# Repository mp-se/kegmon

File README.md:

# KegMon - Monitoring the volume in your kegs

This is a project that I have done for my own Keezer, if you like it please feel free to suggest improvements. 

For docs see: https://mp-se.github.io/kegmon/index.html

# Hardware

* Supports ESP8266 D1 mini, ESP32s2 mini or ESP32s3 mini
* Loadcells and HX711/NAU7802 ADC converters
* DS18B20, DHT22, BME280 or BrewPI(IP) temperature sensors
* OLED 0.96" or LCD 20x4/20x2 displays

# Features

* Can measure weight from 1 or 2 scales
* Stable scale presentation (data is filtered and processed)
* Support temperature/humidity sensor in one scale base
* Integration with Brewfather to retrive data on brew
* Integration with Brewspy to retrive data on brew and also update the remaning volume and pours
* Integration with Home Assistant
* Weights and Volumes in Metric, Imperial (both US and UK)
* Pour detection for pours over 100 ml
* Estimation on how many glasses remain in the kegs
* Firmware update via UI
* One build for all hardware options
* Modern HTML5 UI
* Easy scale calibration
* 3D models and PCB

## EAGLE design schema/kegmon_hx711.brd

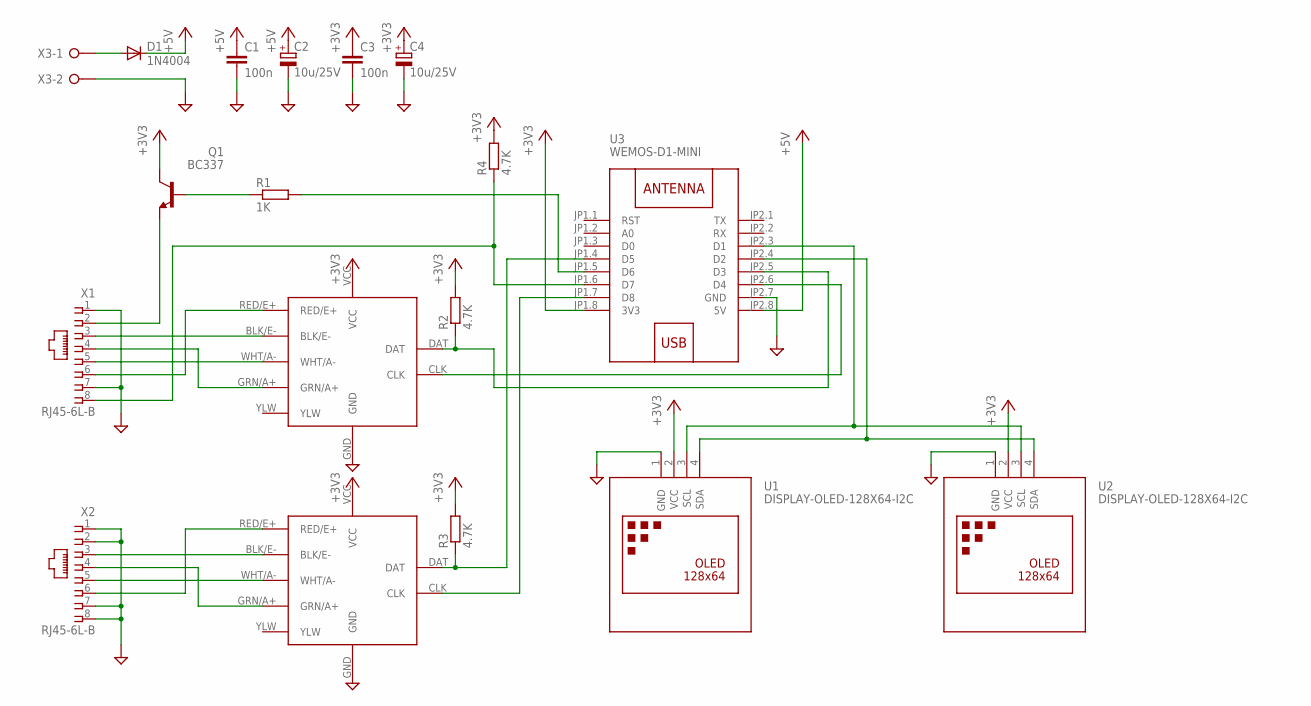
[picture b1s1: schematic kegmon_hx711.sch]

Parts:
C1, C3: 100n; C050-025X075
C2, C4: 10u/25V; E2,5-5
D1: 1N4004; DO41-10
IC1, IC2: SPARKFUN-HX711
Q1: BC337; TO92
R1: 1K; 0207/10
R2, R3, R4: 4.7K; 0207/10
U1, U2: DISPLAY-OLED-128X64-I2C; DISPLAY-OLED-128X64-I2C-NOHOLES
U3: WEMOS-D1-MINI
X1, X2: RJ45-6L-B; RJ45-NO-SHIELD
X3: W237-02P; W237-132

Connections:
+3V3: C3.1, C4.+, IC1.VCC, IC2.VCC, Q1.3 (C), R2.2, R3.2, R4.2, U1.2 (VCC), U2.2 (VCC), U3.JP1.8 (3V3)
+5V: C1.1, C2.+, D1.C, U3.JP2.8 (5V)
GND: C1.2, C2.-, C3.2, C4.-, IC1.GND, IC2.GND, U1.1 (GND), U2.1 (GND), U3.JP2.7 (GND), X1.1, X1.7, X2.1, X2.2, X2.7, X2.8, X3.2
unnamed: Q1.2 (B), R1.1
unnamed: U1.3 (SCL), U2.3 (SCL), U3.JP2.3 (D1)
unnamed: D1.A, X3.1
unnamed: IC1.RED/E+, X1.6
unnamed: IC1.BLK/E-, X1.3
unnamed: R4.1, U3.JP1.6 (D7), X1.8
unnamed: IC1.WHT/A-, X1.5
unnamed: IC1.GRN/A+, X1.4
unnamed: IC2.BLK/E-, X2.3
unnamed: IC2.RED/E+, X2.6
unnamed: IC2.GRN/A+, X2.4
unnamed: IC2.WHT/A-, X2.5
unnamed: IC1.DAT, R2.1, U3.JP2.5 (D3)
unnamed: IC1.CLK, U3.JP2.6 (D4)
unnamed: IC2.DAT, R3.1, U3.JP1.4 (D5)
unnamed: IC2.CLK, U3.JP1.7 (D8)
unnamed: U1.4 (SDA), U2.4 (SDA), U3.JP2.4 (D2)
unnamed: Q1.1 (E), X1.2
unnamed: R1.2, U3.JP1.5 (D6)

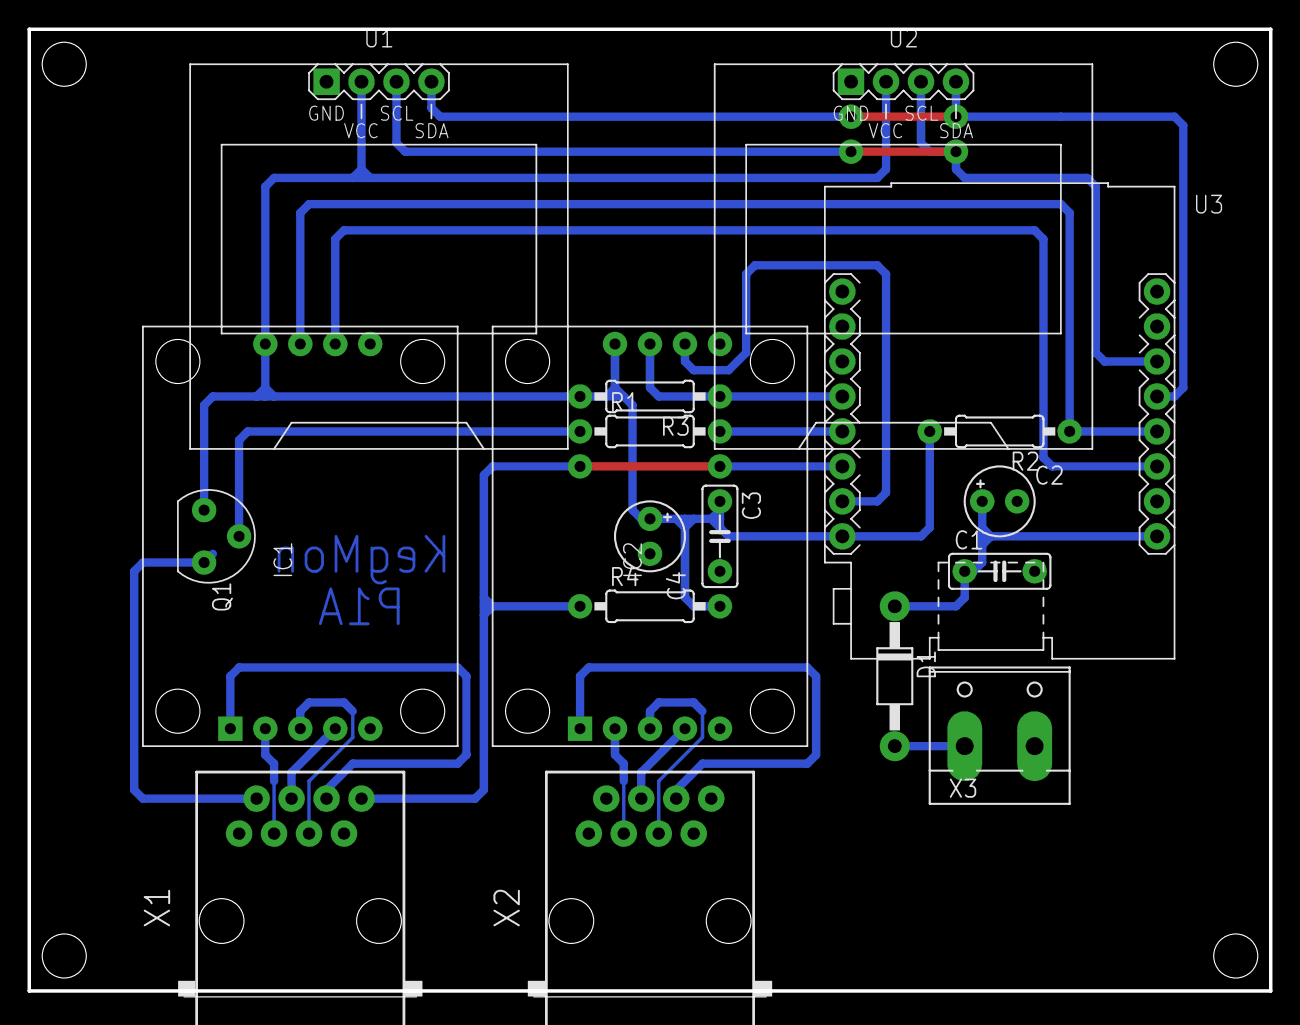
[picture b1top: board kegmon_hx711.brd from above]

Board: 2 copper layers, 90.2 x 69.8 mm, 18 parts (0 on the bottom side), 22 nets.

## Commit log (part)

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2023-03-16 GitHub Action Build
2023-03-16 Increase json buffer size
2023-03-16 Lint fixes
2023-03-16 Update documentation
2023-03-18 Added link to alternative scale base.
2023-03-19 Updated hardware docs
2023-03-20 Removed humidity when ds18b20 is used
2023-03-20 HW doc update
2023-03-20 Updated platformio
2023-03-20 Update doc date
2023-04-11 Adding hardware testing target
2023-04-11 Adding option to bypass scale validations
2023-04-11 Precommit fixes
2023-04-11 Added mobile dashboard
2023-04-11 Added schema and pcb for HX711
2023-04-11 Updated release notes for 0.6
2023-04-11 Updated project config
2023-04-24 Added dashboard, pcb and case
2023-04-27 Updated docs for release
2023-05-04 Added progress bar on dashboard
2023-05-05 Added driver for LCD 20x4
2023-05-05 Added new display option
2023-05-06 Added layout for single display + lcd build
2023-05-06 Fix precommit
2023-05-08 Merged into one build
2023-05-08 0.7b2
2023-05-08 Remove lcb bins
2023-05-10 Updated layout
2023-05-20 Doc updates for LCB
2023-05-20 Refactored display layout into own class
2023-05-20 Adjusted formatting for lcd
2023-05-21 Updated docs with respect to LCD
2023-05-31 Adding cors header to responses
2023-05-31 Adjusted to new display setup
2023-05-31 Update release notes
2023-05-31 Fixed version number for docs
2023-06-10 Remove duplicated define WS_SEND
2023-06-10 Update arduino versions
2023-06-10 Adding log outputs to level change
2023-06-12 Adding reset reason to s2 + fix bug in influx push
2023-06-12 Fix month+1 in loglevels
2023-06-12 Correct use of espserial wss init
2023-06-12 Adjusted hass device registration
2023-06-13 Update arduino version
2023-06-14 Dont send temp to hass if no sensor is attached
2023-06-19 Added core dump option and startup logging
2023-06-19 Skip level logging if values are zero
2023-06-19 Fix include naming
2023-06-19 Added partition file with coredump partition
2023-06-19 Updated build dependecies
2023-07-30 move code around and split sensors
2023-08-03 Added raw weight on hardware stats
2023-08-03 Updated display layout
2023-08-03 Updated build no
2023-08-03 Updated release notes
2023-08-03 Formatting changes
2023-08-04 Update esp fwk
2023-08-05 use unique_ptr and add logs
2023-08-05 check sensor more often
2023-08-05 replace floats
2023-08-05 Updated dependecies
2023-08-07 Fix include error from PR
2023-08-07 Adjused code to work with esp32
2023-08-08 Updated dependecies and cleanup code
2023-08-09 add code
2023-08-09 add docs
2023-08-16 setup on secondery address too
2023-08-16 remove binary changes
2023-08-18 undo reset changes
2023-08-18 fix formating
2023-08-28 Change default temp sensor
2023-08-28 Update docs
2023-08-28 Update dependecies
2023-08-28 Added bme280 support
2023-08-28 Fix bug in level.cpp
2023-08-28 Updated test payload
2023-08-28 Run precommit
2023-08-28 Updated docs
2023-08-30 Adding option to change pins
2023-08-30 Pins are disabled by default
2023-08-30 precommit
2023-08-31 Adding tooltops
2023-08-31 Fixed build for esp32s2
2023-08-31 Fixed reset logic for temp sensors
2023-08-31 bump version
2023-09-02 Fix config url
2023-09-03 Adding support for wokwi
2023-09-03 Upd esp32 deps
2023-09-03 precommit updates
2023-09-04 Update images for docs
2023-09-04 Bump to beta1
2023-09-06 Update for wokwi debug
2023-09-07 Adding development page to docs
2023-09-08 Update gh
2023-09-08 Update gh action
2023-09-10 Added simple dependemcy checker for libraries
2023-09-10 Update gha for build
2023-09-10 Updated dependency checker
2023-09-12 Update dependency script
2023-09-12 Updated dependencies
2023-09-12 Adding env file for act gh runner
2023-09-13 Fixed error message
2023-09-13 Update version + fix json issues + upd gha
2023-10-04 Using pre-built partition as fs for wokwi
2023-10-04 Bump to release
2023-10-04 Adding condition
2023-10-04 Upd doc ver
2023-10-05 Revert arduino version to 5.4
2023-10-12 Fix issue with dht22 sensor not being detected as missing
2023-10-13 Fix memory leak
2023-10-13 Formatting fix
2023-10-21 Adding brewpi as temp sensor
2023-11-08 Removed dashboard
2023-12-18 Added support for s3 board
2023-12-18 Fix precommit errors
2024-01-26 Add s3 to build
2024-01-27 Fix spelling
2024-01-28 Update (c)
2024-07-14 Remove old UI files
2024-07-14 Update brewspy
2024-07-14 Change config to adapat to new tag format
2024-07-14 Updated api's to use 100% json
2024-07-14 Fixed problem when factor could be nan
2024-07-14 Added meethod to check if scheduled tasks is running
2024-07-17 Updates to match new espfwk
2024-07-17 Fix ui repo path
2024-07-17 Update build
2024-07-18 Updates to docs for v1
2024-07-18 Added uptime counter
2024-07-20 Added todo
2024-07-28 Manual s3 build
2024-07-28 Fixed old config conversion
2024-07-28 Fixed uptime refresh
2024-07-28 Added scale connected status
2024-07-28 Move temp init to after wifi
2024-07-29 Remove unused methods
2024-07-29 Increase json document size for config
2024-07-29 Enable influx sending via UI
2024-07-29 Update license
2024-07-29 Remove unused defines
2024-07-30 remove unused file
2024-07-30 Update ui
2024-07-30 Bump ver
2024-07-30 Upd release notes
2024-07-31 Added favicon
2024-07-31 Adding favicon
2024-08-03 Upd build
2024-08-29 Update precommit
2024-08-29 Change wire speed to 400mhz
2024-08-29 Update gitignore
2024-09-09 Added support for barhelper
2024-09-09 Fix html not loading
2024-09-09 Fix config
2024-09-10 Switch to onewireNG
2024-09-10 Added push feedback to UI
2024-09-11 Remove old test data
2024-09-11 Remove unit testing
2024-09-11 Removed unused target
2024-09-11 Switched to non ssl for esp8266 for barhelper
2024-09-29 Added additional attributes to ha integration
2024-09-29 Force build
2024-09-30 Update espfwk
2024-10-21 Adding bf id to config
2024-10-22 Formatting
2024-10-22 Adding brewlogger as new target
2024-10-22 Refactor
2024-10-22 Added brewlogger integration
2024-10-24 Adding maxVol attribute to brewlogger
2024-10-24 Added brewlogger to status
2024-10-24 Fixed url for brewlogger
2024-12-07 Add support for chamber controller
2024-12-26 Migrated to espfwk 1.1 and new dependecies
2024-12-26 Fix hardware scan
2025-09-12 Update dependencies
2025-09-14 Remove unused workflow
2025-09-14 Update (c) yeart
2025-09-14 Remove unsuppored temp sensors
2025-09-14 Remove unsupported scale hardware
2025-09-14 Update config options
2025-09-15 Update flash layout
2025-09-15 Add bord to define script
2025-09-15 Remove obsolete part of docs
2025-09-15 Remove deps to 8266 and fix compiler errors
2025-09-15 Minor update to readme
2025-09-15 Hw testing
2025-09-16 Remove old library
2025-09-16 Update hardware testing code
2025-09-16 Switch to new local hx711 library
2025-09-16 Switch to new hx711 library
2025-09-17 Update hx library
2025-09-17 Update temp sensor interface
2025-09-17 Update to support new hx library
2025-09-17 Update hw test code
2025-09-17 Update main to match scale changes
2025-09-17 Update to hx711 dev branch
2025-12-28 Save state
2026-01-07 Update deps
2026-01-07 Move tinyexpr to lib folder
2026-01-07 Fix const declarations in config
2026-01-07 Temporary comment out level files
2026-01-07 Temporary comment out startup file
2026-01-07 Remove obsolete tempsensor code
2026-01-07 Update temp sensor for DS18B20
2026-01-07 Move tinyexpr from dependency
2026-01-08 Update precommit configuration
2026-01-11 Remove tinyexpr
2026-01-11 Update pre-commit rules
2026-01-11 Remove old code not needed
2026-01-11 Adding filter implementations
2026-01-11 Updated scale interface
2026-01-11 New change level detector with states
2026-01-11 Fixed missed include
2026-01-11 Update config to match new scale handling
2026-01-11 Update change detection
2026-01-11 Update scale
2026-01-11 Addded scale testing
2026-01-11 Update tempsensor class to return sensor id
2026-01-11 Fixed hardcoded scale count
2026-01-11 Fixed hardcode scale count
2026-01-11 Update config file format to use arrays
2026-01-11 Update status, feature and statistics apis
2026-01-11 Cleanup main.hpp
2026-01-11 Use looptimer class
2026-01-12 Refactor DS class to cache sensor ID
2026-01-12 Adding SD card implementation
2026-01-12 Update /scale api
2026-01-12 Remove unused settings in config
2026-01-12 Fixed scale init based on number of scales supported in build
2026-01-13 Changed limits to constants
2026-01-13 Adding invalid weight as event
2026-01-13 Adding min and max valid weight params
2026-01-13 Adding latest events to payload
2026-01-13 Updating project constants
2026-01-14 Added SD card and LVGL UI
2026-01-25 Making copy of 1.x docs
2026-02-01 Fixed version number in docs

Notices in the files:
parts and their libraries:
diy-modules: Released under the Creative Commons Attribution 4.0 International License: http://creativecommons.org/licenses/by/4.0
